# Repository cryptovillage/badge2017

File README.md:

# badge2017

To buld the ESP32 firmware:

1. Install the ESP32 toolchain for your OS. You do not need to install the ESP-IDF -- that happens automatically in the$
  * For Linux: https://esp-idf.readthedocs.io/en/v3.1-beta1/get-started/linux-setup.html
  * For Windows: https://esp-idf.readthedocs.io/en/v3.1-beta1/get-started/windows-setup.html
  * For OSX: https://esp-idf.readthedocs.io/en/v3.1-beta1/get-started/macos-setup.html

2. Pull in the ESP-IDF, MicroPython, and other dependencies:
`git submodule update --init --recursive`

3. Build mpy_cross:
`cd firmware/esp32/components/micropython/micropython/mpy-cross/ && make && cd ../../../..`

4. Optionally configure the serial port that your badge appears on (under Serial Flasher Config):
`make menuconfig`

5. Build it:
`make -j5`

6. Flash it:
`make flash` OR

`python esptool/esptool.py --chip esp32 --port /dev/ttyUSB0 --baud 115200 --before default_reset --after hard_reset write_flash -z --flash_mode dio --flash_freq 40m --flash_size detect 0x1000 bootloader.bin 0x10000 cpv2017.bin 0x8000 partitions.bin`

you may need to replace /dev/ttyUSB0 with /dev/ttyACM0 or whatever serial device the badge is listed as.

You can edit the build configuration with (includes wifi creds):

`make menuconfig`

SD Card contents can be found: https://2017.badge.cryptovillage.org/sdcard/0.3-prerel.zip

If your device is showing "TEST MODE", the EFM8 needs to be flashed. We've found that this only works from a Windows computer or Virtualbox with the Extension Pack for USB devices. If using a VM, we found that the IE11 Win7 testing VM from MicroSoft worked. You will need to install the driver from: https://www.silabs.com/products/development-tools/software/usb-to-uart-bridge-vcp-drivers

Download the flashing tools here: https://2017.badge.cryptovillage.org/W18779AXC7/TestFlash.zip

The prebuilt firmware can be found here: https://2017.badge.cryptovillage.org/firmware/v0.9/

You need to replace esp32test.bin with cpv2017.bin, and partitions_singleapp.bin with partitions.bin in TestFlash after unzipping. (Keeping the original filenames from TestFlash.zip contents but replacing the file content)

Hold down the knob when plugging the device in to put the device into a mode to flash the EFM8. The LEDs should not turn on and the screen will be blank and dim.

Run efm8load.exe to flash the EFM8. The device should reboot, but may require replugging in the USB cable. It should now appear as a serial device.

Then run NodeMCU-PyFlasher.exe to flash the ESP32.

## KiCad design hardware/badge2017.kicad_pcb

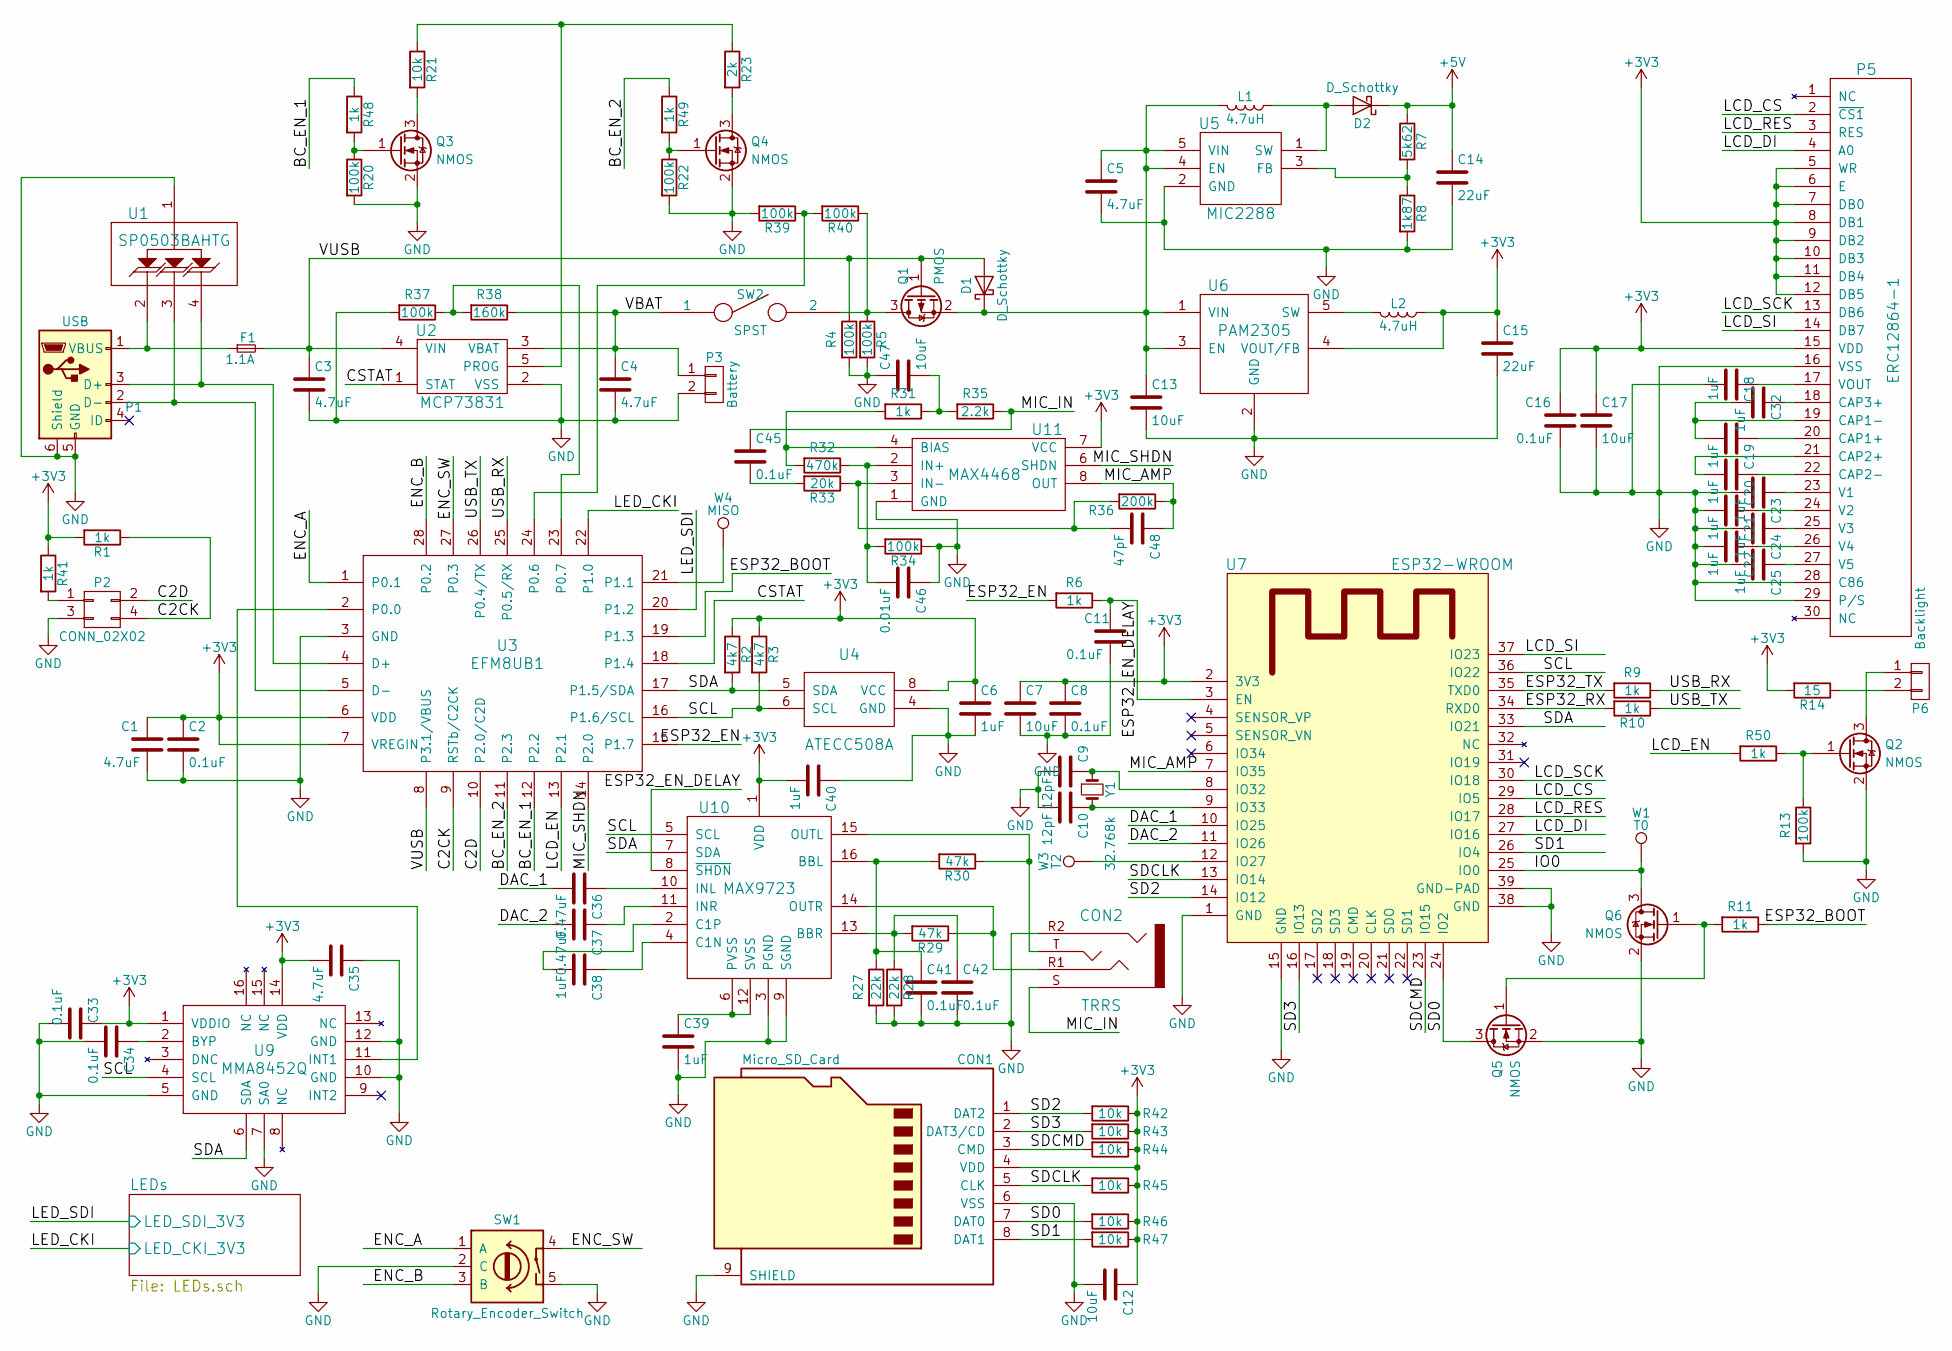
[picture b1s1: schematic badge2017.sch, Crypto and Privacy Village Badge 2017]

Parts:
C1, C35: 4.7uF; C_0603; Tolerance +/- 20%; Voltage 6.3V
C2, C8, C11, C16, C33, C34: 0.1uF; C_0603; Tolerance +/- 20%; Voltage 6.3V
C3, C4, C5: 4.7uF; C_0603; Tolerance +/- 20%; Voltage 16V
C6, C38, C40: 1uF; C_0603; Tolerance +/- 20%; Voltage 6.3V
C7, C12, C17, C47: 10uF; C_0603; Tolerance +/- 20%; Voltage 6.3V
C9, C10: 12pF; C_0603; Tolerance +/- 10%; Voltage 6.3V
C13: 10uF; C_0603; Tolerance +/- 20%; Voltage 16V
C14, C15: 22uF; C_0603; Tolerance +/- 20%; Voltage 10V
C18, C19, C20, C21, C22, C23, C24, C25, C32: 1uF; C_0603; Tolerance +/- 20%; Voltage 25V
C36, C37: 0.47uF; C_0603; Tolerance +/- 10%; Voltage 6.3V
C39: 1uF; C_0603; Tolerance +/- 20%; Voltage 16V
C41, C42, C45: 0.1uF; C_0603; Tolerance +/- 10%; Voltage 6.3V
C46: 0.01uF; C_0603; Tolerance +/- 10%; Voltage 6.3V
C48: 47pF; C_0603; Tolerance +/- 10%; Voltage 6.3V
CON1: Micro_SD_Card; MICROSD; MfgPartNum 472192001
CON2: TRRS; TRRS_jack; MfgPartNum SJ-43516-SMT-TR
D1, D2: D_Schottky; SOD-323; MfgPartNum BAT20JFILM
F1: 1.1A; R_1210; MfgPartNum MF-USMF110-2
L1, L2: 4.7uH; R_0603; MfgPartNum LQM21PN4R7MGSD
P1: USB; USB_Micro-B-cpv; MfgPartNum 10118192-0001LF
P2: CONN_02X02; Socket_Strip_Straight_2x02_TP
P3: Battery; JST_PH_SMD
P5: ERC12864-1; LCD_zif_connector
P6: Backlight; JST_PH_SMD
Q1: PMOS; SOT-23; MfgPartNum DMG2307L-7
Q2, Q3, Q4, Q5, Q6: NMOS; SOT-23; MfgPartNum MMBF170
R1, R6, R9, R10, R11, R41, R48, R49, R50: 1k; R_0603
R2, R3: 4k7; R_0603; Tolerance 0.1
R4, R5, R13, R20, R22: 100k; R_0603
R7: 5k62; R_0603; Tolerance 0.02
R8: 1k87; R_0603; Tolerance 0.02
R14: 15; R_0603; Tolerance 0.1
R21: 10k; R_0603; Tolerance 0.05
R23: 2k; R_0603; Tolerance 0.05
R27, R28: 22k; R_0603; Tolerance 0.05
R29, R30: 47k; R_0603; Tolerance 0.05
R31: 1k; R_0603; Tolerance 0.05
R32: 470k; R_0603; Tolerance 0.05
R33: 20k; R_0603; Tolerance 0.05
R34, R37, R39, R40: 100k; R_0603; Tolerance 0.05
R35: 2.2k; R_0603; Tolerance 0.05
R36: 200k; R_0603; Tolerance 0.05
R38: 160k; R_0603; Tolerance 0.05
R42, R43, R44, R45, R46, R47: 10k; R_0603
SW1: Rotary_Encoder_Switch; EN12_RotaryEncoder; MfgPartNum EN12-HS22AF20
SW2: SPST; DPDT_SMD; MfgPartNum JS202011SCQN
U1: SP0503BAHTG; SOT-143; MfgPartNum SP0503BAHTG
U2: MCP73831; SOT-23-5; MfgPartNum MCP73831T-2ACI/OT
U3: EFM8UB1; QFN-28-1EP_5x5mm_Pitch0.5mm; MfgPartNum EFM8UB10F16G-C-QFN28
U4: ATECC508A; SOIC-8_3.9x4.9mm_Pitch1.27mm; MfgPartNum ATECC508A-SSHDA-B
U5: MIC2288; SOT-23-5; MfgPartNum MIC2288YD5-TR
U6: PAM2305; SOT-23-5; MfgPartNum PAM2305AAB330
U7: ESP32-WROOM; MfgPartNum ESP-WROOM-32
U9: MMA8452Q; MfgPartNum MMA8452QT
U10: MAX9723; QFN-16-1EP_4x4mm_Pitch0.65mm; MfgPartNum MAX9723DETE+
U11: MAX4468; SOT-23-8; MfgPartNum MAX4468EKA+T
W1: T0; Measurement_Point_Round-SMD-Pad_Small
W3: T2; Measurement_Point_Round-SMD-Pad_Small
W4: MISO; Measurement_Point_Round-SMD-Pad_Small
Y1: 32.768k; abs25_crystal; MfgPartNum ABS25-32.768KHZ-T

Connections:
+3V3: C1.1, C2.1, C6.1, C7.1, C8.1, C12.1, C15.1, C16.1, C17.1, C33.1, C35.2, C40.2, CON1.4 (VDD), L2.1, P5.5 (WR), P5.6 (E), P5.7 (DB0), P5.8 (DB1), P5.9 (DB2), P5.10 (DB3), P5.11 (DB4), P5.12 (DB5), P5.15 (VDD), R1.2, R2.1, R3.1, R14.2, R41.1, R42.1, R43.1, R44.1, R45.1, R46.1, R47.1, U3.6 (VDD), U3.7 (VREGIN), U4.8 (VCC), U6.4 (VOUT/FB), U7.2 (3V3), U9.1 (VDDIO), U9.14 (VDD), U10.1 (VDD), U11.7 (VCC)
+5V: C14.1, D2.1 (K), R7.1; also elsewhere on the board
/BC_EN_1: R48.1, U3.12 (P2.2)
/BC_EN_2: R49.1, U3.11 (P2.3)
/C2CK: P2.4, R1.1, U3.9 (RSTb/C2CK)
/C2D: P2.2, U3.10 (P2.0/C2D)
/CSTAT: U2.1 (STAT), U3.18 (P1.4)
/DAC_1: C36.2, U7.10 (IO25)
/DAC_2: C37.2, U7.11 (IO26)
/ENC_A: SW1.1 (A), U3.1 (P0.1)
/ENC_B: SW1.3 (B), U3.28 (P0.2)
/ENC_SW: SW1.4, U3.27 (P0.3)
/ESP32_BOOT: R11.1, U3.19 (P1.3)
/ESP32_EN: R6.2, U3.15 (P1.7)
/ESP32_EN_DELAY: C11.1, R6.1, U7.3 (EN), U10.8 (~SHDN)
/ESP32_RX: R10.2, U7.34 (RXD0)
/ESP32_TX: R9.2, U7.35 (TXD0)
/IO0: Q6.3 (D), U7.25 (IO0), W1.1
/LCD_CS: P5.2 (~CS1), U7.29 (IO5)
/LCD_DI: P5.4 (A0), U7.27 (IO16)
/LCD_EN: R50.2, U3.13 (P2.1)
/LCD_RES: P5.3 (RES), U7.28 (IO17)
/LCD_SCK: P5.13 (DB6), U7.30 (IO18)
/LCD_SI: P5.14 (DB7), U7.37 (IO23)
/LED_CKI: U3.22 (P1.0); also elsewhere on the board
/LED_SDI: U3.20 (P1.2); also elsewhere on the board
/MIC_AMP: C48.1, R36.1, U7.7 (IO35), U11.8 (OUT)
/MIC_IN: C45.1, CON2.S, R35.1
/MIC_SHDN: U3.14 (P2.0), U11.6 (SHDN)
/SCL: R3.2, U3.16 (P1.6/SCL), U4.6 (SCL), U7.36 (IO22), U9.4 (SCL), U10.5 (SCL)
/SD0: CON1.7 (DAT0), Q5.3 (D), R46.2, U7.24 (IO2)
/SD1: CON1.8 (DAT1), R47.2, U7.26 (IO4)
/SD2: CON1.1 (DAT2), R42.2, U7.14 (IO12)
/SD3: CON1.2 (DAT3/CD), R43.2, U7.16 (IO13)
/SDA: R2.2, U3.17 (P1.5/SDA), U4.5 (SDA), U7.33 (IO21), U9.6 (SDA), U10.7 (SDA)
/SDCLK: CON1.5 (CLK), R45.2, U7.13 (IO14)
/SDCMD: CON1.3 (CMD), R44.2, U7.23 (IO15)
/USB_RX: R9.1, U3.25 (P0.5/RX)
/USB_TX: R10.1, U3.26 (P0.4/TX)
/VBAT: C4.1, P3.1, R38.1, SW2.1, U2.3 (VBAT)
/VUSB: C3.1, D1.2 (A), F1.2, Q1.1 (G), R4.1, U2.4 (VIN), U3.8 (P3.1/VBUS)
GND: C1.2, C2.2, C3.2, C4.2, C5.2, C6.2, C7.2, C8.2, C9.2, C10.2, C11.2, C12.2, C13.2, C14.2, C15.2, C16.2, C17.2, C18.2, C21.2, C22.2, C23.2, C24.2, C25.2, C33.2, C34.2, C35.1, C39.2, C40.1, C41.2, C42.2, C46.1, C47.1, CON1.6 (VSS), CON1.9 (SHIELD), CON2.R2, P1.5 (GND), P1.6 (Shield), P2.3, P3.2, P5.16 (VSS), P5.28 (C86), P5.29 (P/S), Q2.2 (S), Q3.2 (S), Q4.2 (S), Q5.2 (S), Q6.2 (S), R4.2, R5.2, R8.2, R13.2, R20.2, R22.2, R27.2, R28.2, R34.1, R37.2, R39.2, SW1.2 (C), SW1.5, U1.1, U2.2 (VSS), U3.3 (GND), U4.4 (GND), U5.2 (GND), U6.2 (GND), U7.1 (GND), U7.15 (GND), U7.38 (GND), U7.39 (GND-PAD), U9.5 (GND), U9.7 (SA0), U9.10 (GND), U9.12 (GND), U10.3 (PGND), U10.9 (SGND), U11.1 (GND); also elsewhere on the board
unnamed: C9.1, U7.8 (IO32), Y1.1
unnamed: C10.1, U7.9 (IO33), Y1.2
unnamed: C5.1, C13.1, D1.1 (K), L1.2, Q1.2 (S), U5.4 (EN), U5.5 (VIN), U6.1 (VIN), U6.3 (EN)
unnamed: C18.1, P5.17 (VOUT)
unnamed: C19.1, P5.20 (CAP1+)
unnamed: C19.2, C32.2, P5.19 (CAP1-)
unnamed: C20.1, P5.22 (CAP2-)
unnamed: C20.2, P5.21 (CAP2+)
unnamed: C21.1, P5.24 (V2)
unnamed: C22.1, P5.26 (V4)
unnamed: C23.1, P5.23 (V1)
unnamed: C24.1, P5.25 (V3)
unnamed: C25.1, P5.27 (V5)
unnamed: C32.1, P5.18 (CAP3+)
unnamed: C34.1, U9.2 (BYP)
unnamed: C36.1, U10.10 (INL)
unnamed: C37.1, U10.11 (INR)
unnamed: C38.1, U10.4 (C1N)
unnamed: C38.2, U10.2 (C1P)
unnamed: C39.1, U10.6 (PVSS), U10.12 (SVSS)
unnamed: C41.1, R27.1, R30.2, U10.16 (BBL)
unnamed: C42.1, R28.1, R29.2, U10.13 (BBR)
unnamed: C45.2, R33.2
unnamed: C46.2, R32.1, R34.2, U11.2 (IN+)
unnamed: C47.2, R31.1, R35.2
unnamed: C48.2, R33.1, R36.2, U11.3 (IN-)
unnamed: CON2.R1, R29.1, U10.14 (OUTR)
unnamed: CON2.T, R30.1, U10.15 (OUTL)
unnamed: D2.2 (A), L1.1, U5.1 (SW)
unnamed: F1.1, P1.1 (VBUS), U1.2
unnamed: L2.2, U6.5 (SW)
unnamed: P1.2 (D-), U1.3, U3.5 (D-)
unnamed: P1.3 (D+), U1.4, U3.4 (D+)
unnamed: P2.1, R41.2
unnamed: P6.1, Q2.3 (D)
unnamed: P6.2, R14.1
unnamed: Q1.3 (D), R5.1, R40.1, SW2.2
unnamed: Q2.1 (G), R13.1, R50.1
unnamed: Q3.1 (G), R20.1, R48.2
unnamed: Q3.3 (D), R21.2
unnamed: Q4.1 (G), R22.1, R49.2
unnamed: Q4.3 (D), R23.2
unnamed: Q5.1 (G), Q6.1 (G), R11.2
unnamed: R7.2, R8.1, U5.3 (FB)
unnamed: R21.1, R23.1, U2.5 (PROG)
unnamed: R31.2, R32.2, U11.4 (BIAS)
unnamed: R37.1, R38.2, U3.23 (P0.7)
unnamed: R39.1, R40.2, U3.24 (P0.6)
unnamed: U3.2 (P0.0), U9.11 (INT1)
unnamed: U3.21 (P1.1), W4.1
unnamed: U7.12 (IO27), W3.1

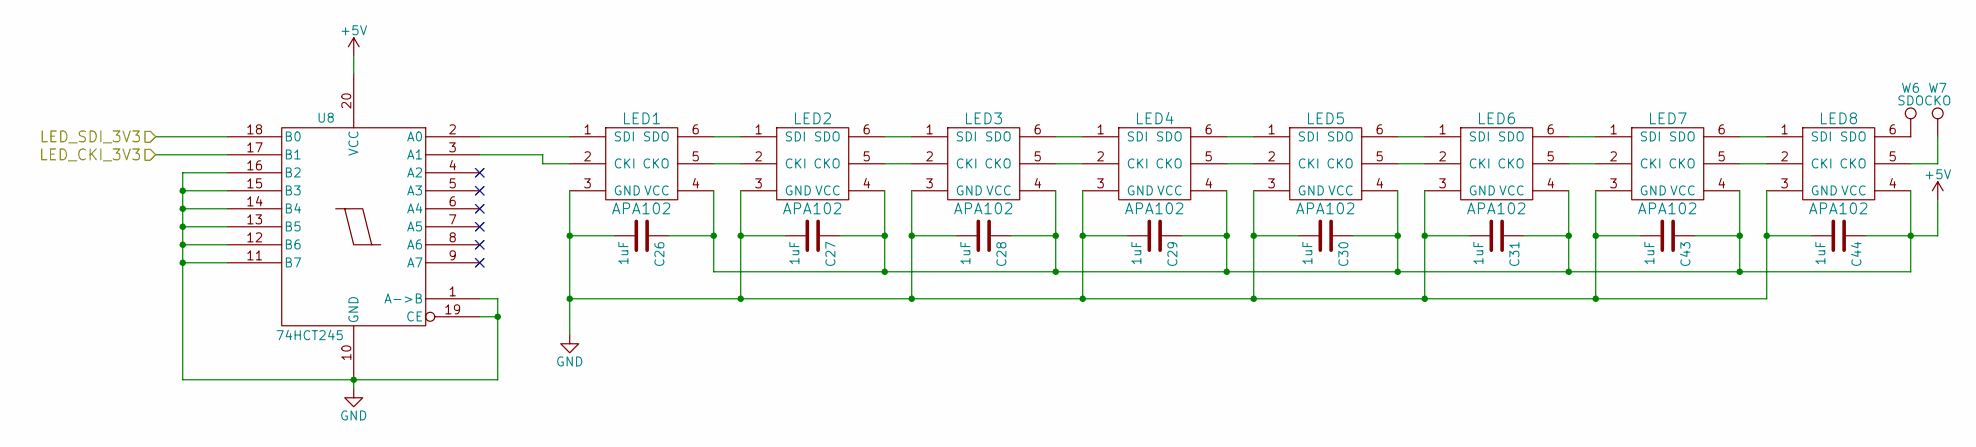
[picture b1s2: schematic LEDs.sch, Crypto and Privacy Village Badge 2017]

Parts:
C26, C27, C28, C29, C30, C31, C43, C44: 1uF; C_0603; Voltage 16V
LED1, LED2, LED3, LED4, LED5, LED6, LED7, LED8: APA102; APA102-2020
U8: 74HCT245; TSSOP-20_4.4x6.5mm_Pitch0.65mm; MfgPartNum 74HCT245PW,118
W6: SDO; Measurement_Point_Round-SMD-Pad_Small
W7: CKO; Measurement_Point_Round-SMD-Pad_Small

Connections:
+5V: C26.1, C27.1, C28.1, C29.1, C30.1, C31.1, C43.1, C44.1, LED1.4 (VCC), LED2.4 (VCC), LED3.4 (VCC), LED4.4 (VCC), LED5.4 (VCC), LED6.4 (VCC), LED7.4 (VCC), LED8.4 (VCC), U8.20 (VCC); also elsewhere on the board
/LED_CKI: U8.17 (B1); also elsewhere on the board
/LED_SDI: U8.18 (B0); also elsewhere on the board
GND: C26.2, C27.2, C28.2, C29.2, C30.2, C31.2, C43.2, C44.2, LED1.3 (GND), LED2.3 (GND), LED3.3 (GND), LED4.3 (GND), LED5.3 (GND), LED6.3 (GND), LED7.3 (GND), LED8.3 (GND), U8.1 (A->B), U8.10 (GND), U8.11 (B7), U8.12 (B6), U8.13 (B5), U8.14 (B4), U8.15 (B3), U8.16 (B2), U8.19 (CE); also elsewhere on the board
unnamed: LED1.1 (SDI), U8.2 (A0)
unnamed: LED1.2 (CKI), U8.3 (A1)
unnamed: LED1.5 (CKO), LED2.2 (CKI)
unnamed: LED1.6 (SDO), LED2.1 (SDI)
unnamed: LED2.5 (CKO), LED3.2 (CKI)
unnamed: LED2.6 (SDO), LED3.1 (SDI)
unnamed: LED3.5 (CKO), LED4.2 (CKI)
unnamed: LED3.6 (SDO), LED4.1 (SDI)
unnamed: LED4.5 (CKO), LED5.2 (CKI)
unnamed: LED4.6 (SDO), LED5.1 (SDI)
unnamed: LED5.5 (CKO), LED6.2 (CKI)
unnamed: LED5.6 (SDO), LED6.1 (SDI)
unnamed: LED6.5 (CKO), LED7.2 (CKI)
unnamed: LED6.6 (SDO), LED7.1 (SDI)
unnamed: LED7.5 (CKO), LED8.2 (CKI)
unnamed: LED7.6 (SDO), LED8.1 (SDI)
unnamed: LED8.5 (CKO), W7.1
unnamed: LED8.6 (SDO), W6.1

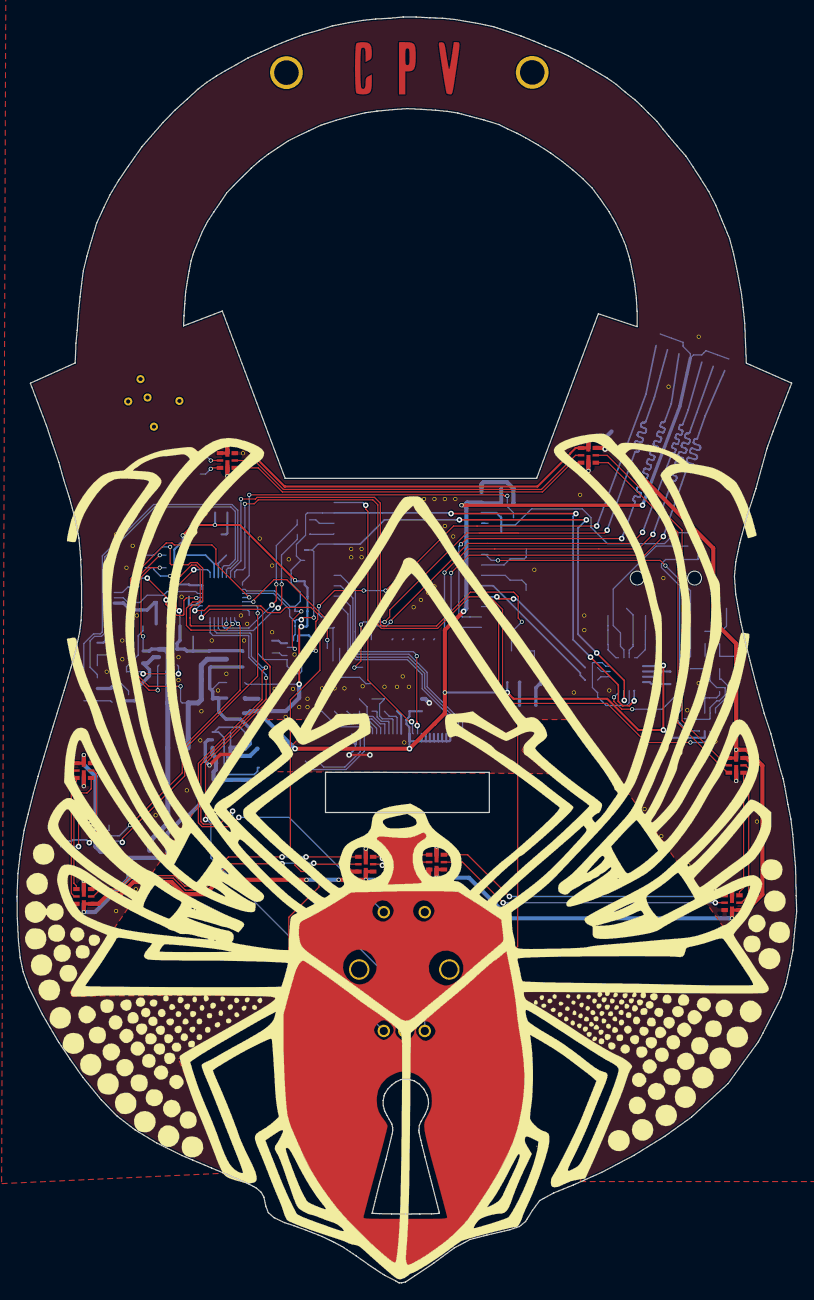
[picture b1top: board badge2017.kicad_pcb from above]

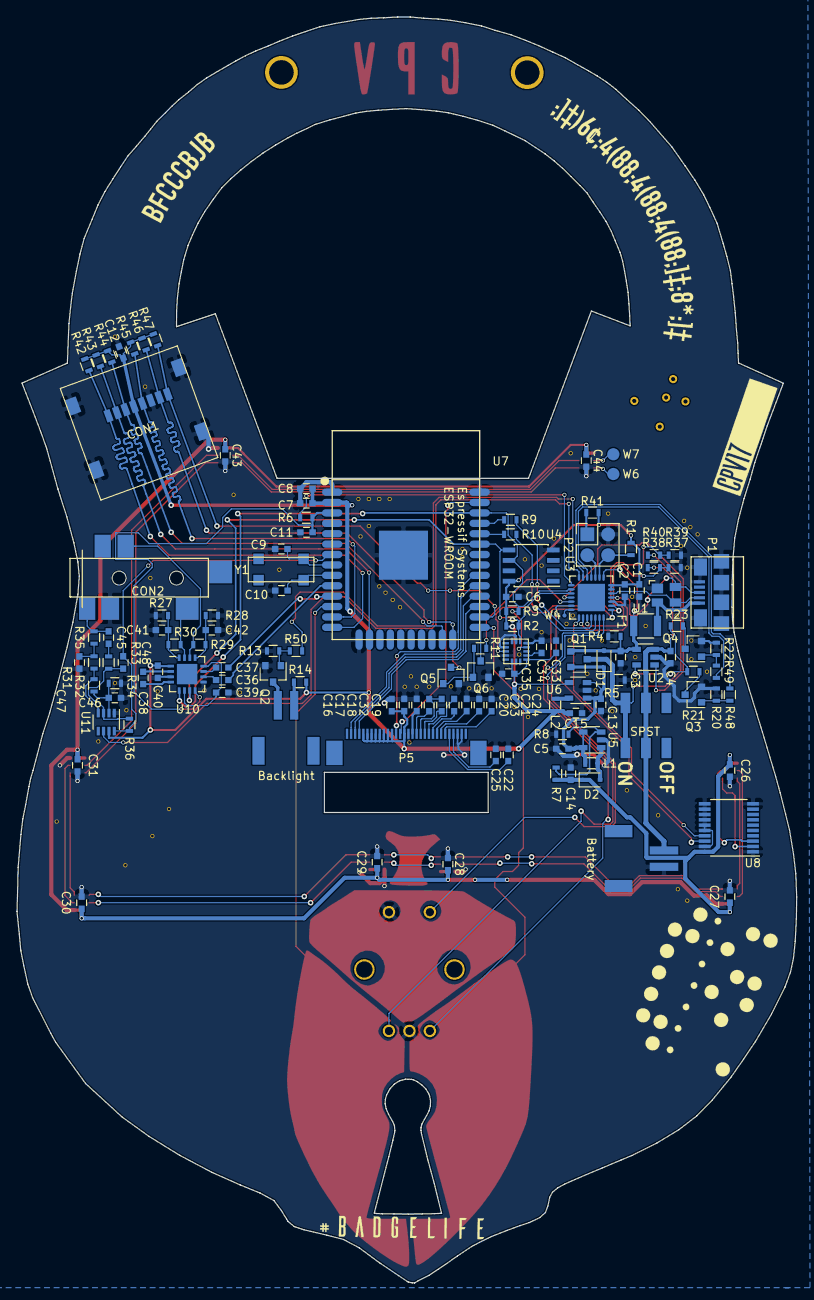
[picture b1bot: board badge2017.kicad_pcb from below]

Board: 2 copper layers, 95.2 x 154.5 mm, 138 parts (123 on the bottom side), 111 nets.

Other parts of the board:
LCD: LCD_outline
W2: T1; Measurement_Point_Round-SMD-Pad_Small
hole_l: hole
hole_l#2: hole

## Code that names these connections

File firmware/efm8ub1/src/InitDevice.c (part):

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	// $[P1MAT - Port 1 Match]
	// [P1MAT - Port 1 Match]$

	ESP32_EN = 0; // Disable ESP32 for now
	ESP32_BOOT = ESP32_BOOT_IDLE; // Don't enable BOOT pulldown
}

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	// $[P2MAT - Port 2 Match]
	// [P2MAT - Port 2 Match]$

	MIC_SHDN = 1; // Shut down MIC amp for now
	BC_EN_1 = 0; // Disable charging
	BC_EN_2 = 0; // Disable charging
}

extern void ADC_0_enter_DefaultMode_from_RESET(void) {
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
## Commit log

2017-07-29 Initial commit of the CPV2017 badge
2018-01-18 minor shamir secret sharing fixes
2018-04-07 Add PDF of schematic
    Generated at `652a2a4b5817ec8460a86f6de45b01e074974e11`
2019-05-06 Use the public CPV fork of micropython
2019-05-06 Switch protocols from git to https for getting the micropython submodule
2019-06-03 Bump esp-idf version to fix nghttp dependency
2019-06-03 Bump micropython version to fix compiler crankyness
2019-06-03 Micropython glue updates
2019-06-04 Add support for polling EFM8 power status
2019-06-09 Bump esp-idf to v3.2
2021-01-20 Update BOM
